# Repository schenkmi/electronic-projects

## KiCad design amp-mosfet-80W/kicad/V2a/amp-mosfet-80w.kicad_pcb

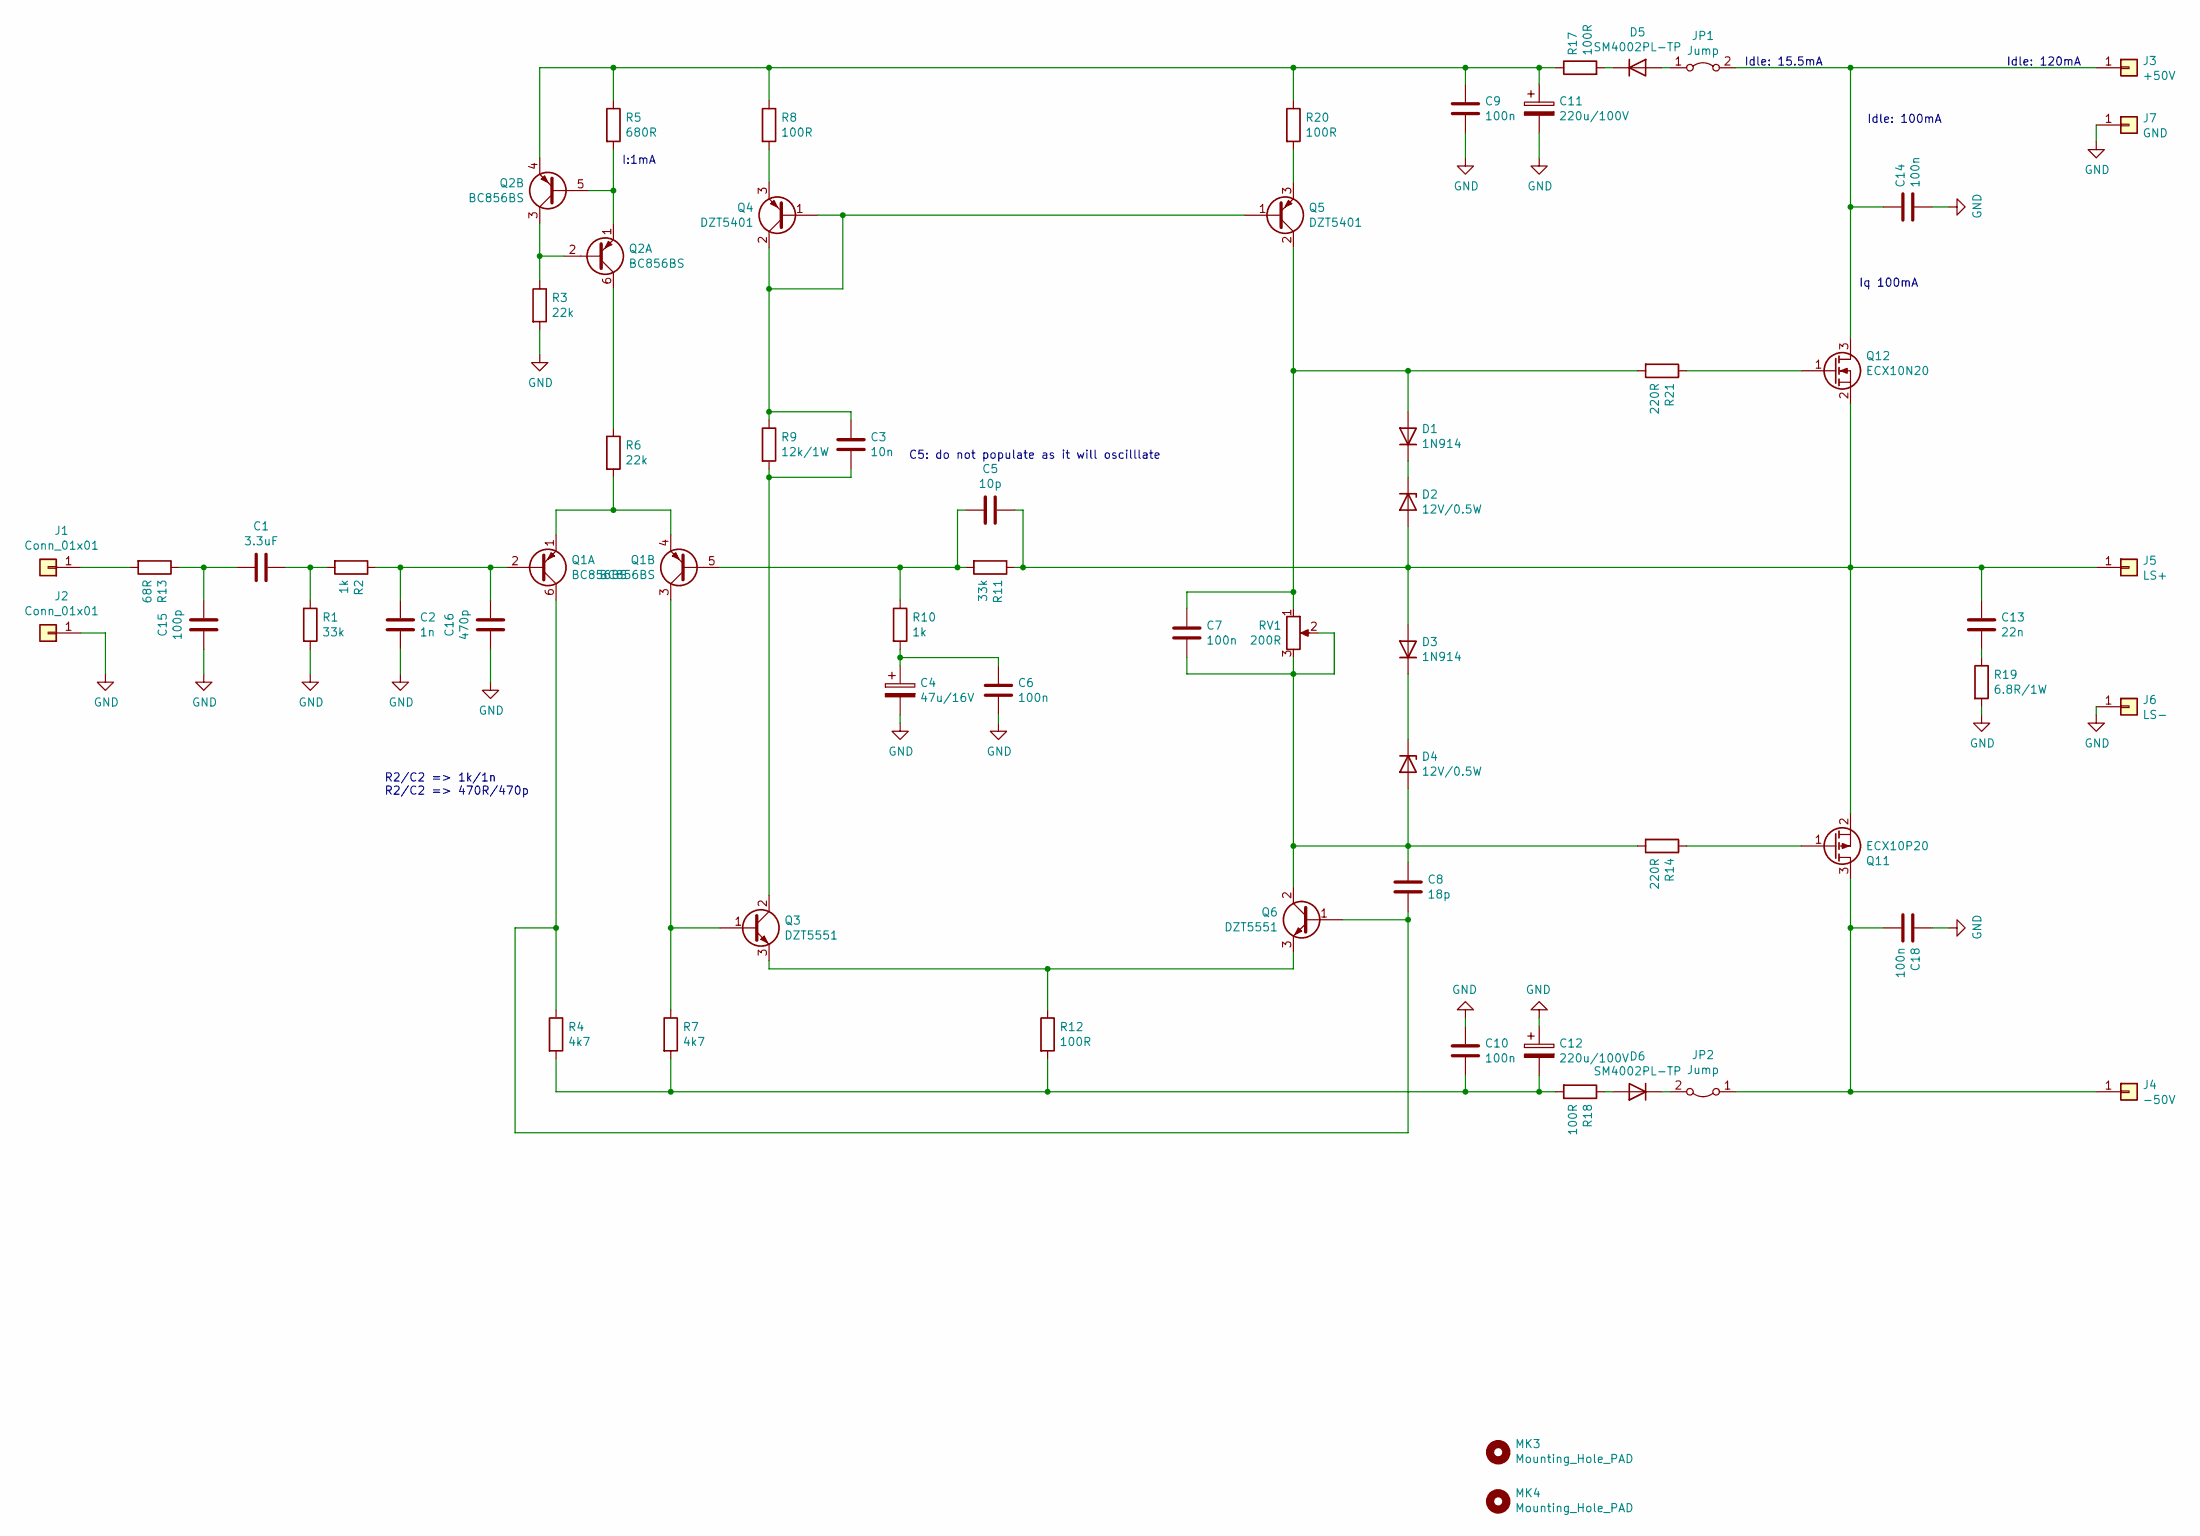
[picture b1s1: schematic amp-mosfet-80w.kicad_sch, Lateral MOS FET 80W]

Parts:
C1: 3.3uF; C_Rect_L7.2mm_W7.2mm_P5.00mm_FKS2_FKP2_MKS2_MKP2
C2: 1n; C_Rect_L7.2mm_W2.5mm_P5.00mm_FKS2_FKP2_MKS2_MKP2
C3: 10n; C_Rect_L7.2mm_W2.5mm_P5.00mm_FKS2_FKP2_MKS2_MKP2
C4: 47u/16V; CP_Radial_D5.0mm_P2.00mm
C5: 10p; C_0805_2012Metric_Pad1.18x1.45mm_HandSolder
C6, C7, C9, C10, C14, C18: 100n; C_Rect_L7.2mm_W2.5mm_P5.00mm_FKS2_FKP2_MKS2_MKP2
C8: 18p; C_0805_2012Metric_Pad1.18x1.45mm_HandSolder
C11, C12: 220u/100V; CP_Radial_D12.5mm_P5.00mm
C13: 22n; C_Rect_L7.2mm_W2.5mm_P5.00mm_FKS2_FKP2_MKS2_MKP2
C15: 100p; C_0805_2012Metric_Pad1.18x1.45mm_HandSolder
C16: 470p; C_0805_2012Metric_Pad1.18x1.45mm_HandSolder
D1, D3: 1N914; D_SOD-123
D2, D4: 12V/0.5W; D_SOD-123
D5, D6: SM4002PL-TP; D_SOD-123F
J1, J2: Conn_01x01; Pin_D1.0mm_L10.0mm
J3: +50V; SolderWire-1.5sqmm_1x01_D1.7mm_OD3.9mm
J4: -50V; SolderWire-1.5sqmm_1x01_D1.7mm_OD3.9mm
J5: LS+; SolderWire-1.5sqmm_1x01_D1.7mm_OD3.9mm
J6: LS-; SolderWire-1.5sqmm_1x01_D1.7mm_OD3.9mm
J7: GND; SolderWire-1.5sqmm_1x01_D1.7mm_OD3.9mm
JP1, JP2: Jump; PinHeader_1x02_P2.54mm_Vertical
MK3, MK4: Mounting_Hole_PAD; MountingHole_3.2mm_M3_Pad_Via
Q1, Q2: BC856BS; SOT-363_SC-70-6
Q3, Q6: DZT5551; SOT-223-3_TabPin2
Q4, Q5: DZT5401; SOT-223-3_TabPin2
Q11: ECX10P20; TO-247-3_Horizontal_TabUp
Q12: ECX10N20; TO-247-3_Horizontal_TabUp
R1, R11: 33k; R_0805_2012Metric_Pad1.20x1.40mm_HandSolder
R2, R10: 1k; R_0805_2012Metric_Pad1.20x1.40mm_HandSolder
R3, R6: 22k; R_0805_2012Metric_Pad1.20x1.40mm_HandSolder
R4, R7: 4k7; R_0805_2012Metric_Pad1.20x1.40mm_HandSolder
R5: 680R; R_0805_2012Metric_Pad1.20x1.40mm_HandSolder
R8, R12, R17, R18, R20: 100R; R_0805_2012Metric_Pad1.20x1.40mm_HandSolder
R9: 12k/1W; R_1206_3216Metric_Pad1.30x1.75mm_HandSolder
R13: 68R; R_0805_2012Metric_Pad1.20x1.40mm_HandSolder
R14, R21: 220R; R_0805_2012Metric_Pad1.20x1.40mm_HandSolder
R19: 6.8R/1W; R_MELF_MMB-0207
RV1: 200R; Potentiometer_Bourns_3296W_Vertical

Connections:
GND: C2.2, C4.2, C6.2, C9.2, C10.1, C11.2, C12.1, C14.2, C15.2, C16.2, C18.1, J2.1, J6.1, J7.1, R1.2, R3.2, R19.2
unnamed: C1.1, R1.1, R2.2
unnamed: C1.2, C15.1, R13.1
unnamed: C3.1, Q4.1 (B), Q4.2 (C), Q5.1 (B), R9.1
unnamed: C3.2, Q3.2 (C), R9.2
unnamed: C4.1, C6.1, R10.2
unnamed: C5.2, Q1.5 (B2), R10.1, R11.2
unnamed: C7.1, C8.2, D4.2 (A), Q6.2 (C), R14.2, RV1.2, RV1.3
unnamed: C7.2, D1.2 (A), Q5.2 (C), R21.2, RV1.1
unnamed: C8.1, Q1.6 (C1), Q6.1 (B), R4.1
unnamed: C10.2, C12.2, R4.2, R7.2, R12.2, R18.2
unnamed: C9.1, C11.1, Q2.4 (E2), R5.1, R8.1, R17.1, R20.1
unnamed: C5.1, C13.1, D2.2 (A), D3.2 (A), J5.1, Q11.2 (D), Q12.2 (S), R11.1
unnamed: C13.2, R19.1
unnamed: C14.1, J3.1, JP1.2 (B), Q12.3 (D)
unnamed: C2.1, C16.1, Q1.2 (B1), R2.1
unnamed: C18.2, J4.1, JP2.1 (A), Q11.3 (S)
unnamed: D1.1 (K), D2.1 (K)
unnamed: D3.1 (K), D4.1 (K)
unnamed: D5.1 (K), R17.2
unnamed: D5.2 (A), JP1.1 (A)
unnamed: D6.1 (K), JP2.2 (B)
unnamed: D6.2 (A), R18.1
unnamed: J1.1, R13.2
unnamed: Q1.1 (E1), Q1.4 (E2), R6.2
unnamed: Q1.3 (C2), Q3.1 (B), R7.1
unnamed: Q2.1 (E1), Q2.5 (B2), R5.2
unnamed: Q2.2 (B1), Q2.3 (C2), R3.1
unnamed: Q2.6 (C1), R6.1
unnamed: Q3.3 (E), Q6.3 (E), R12.1
unnamed: Q4.3 (E), R8.2
unnamed: Q5.3 (E), R20.2
unnamed: Q11.1 (G), R14.1
unnamed: Q12.1 (G), R21.1

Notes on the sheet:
C5: do not populate as it will oscilllate
Idle: 100mA
Iq 100mA
Idle: 15.5mA
Idle: 120mA
I:1mA
R2/C2 => 1k/1n R2/C2 => 470R/470p

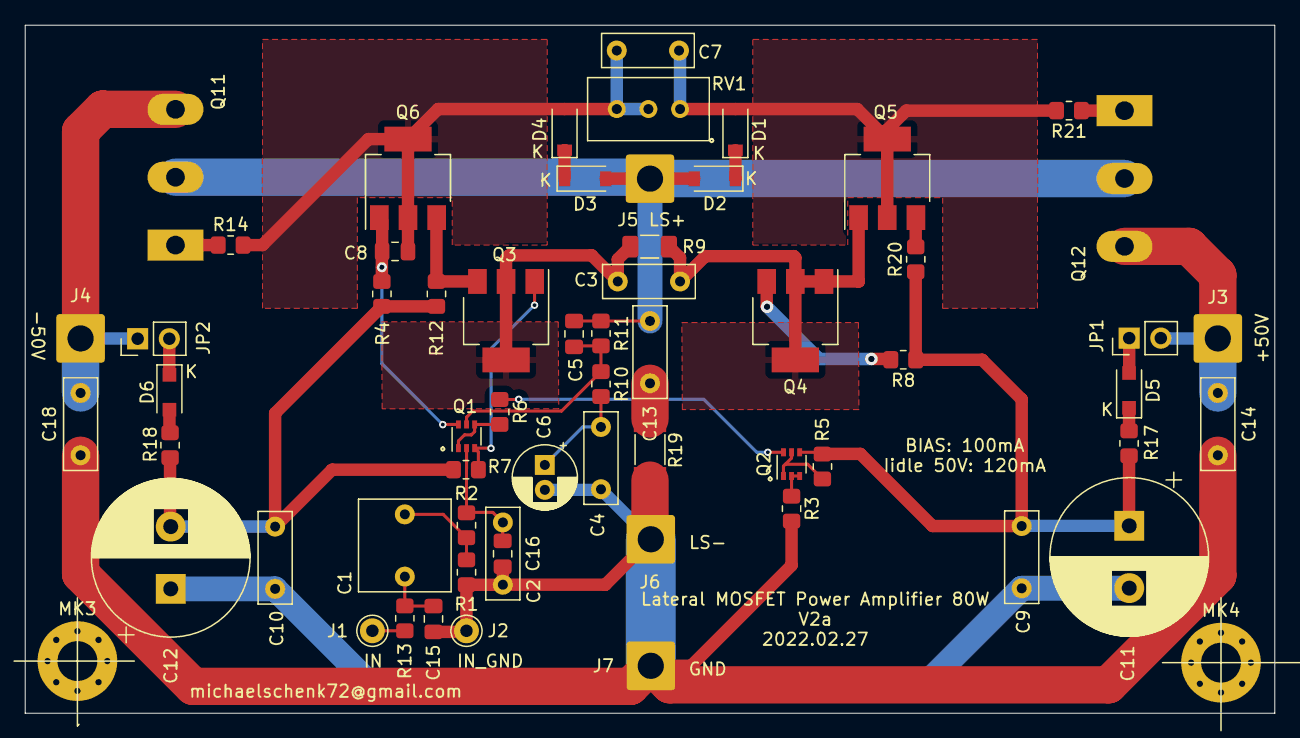
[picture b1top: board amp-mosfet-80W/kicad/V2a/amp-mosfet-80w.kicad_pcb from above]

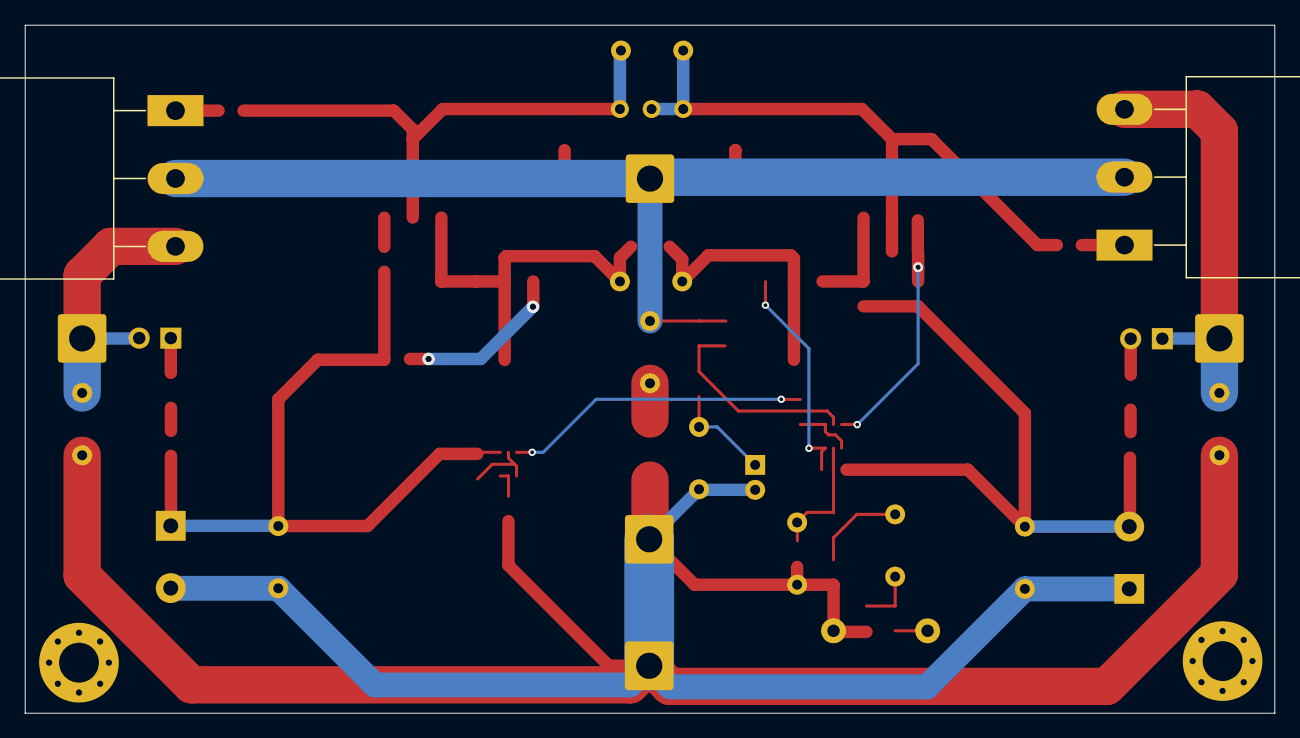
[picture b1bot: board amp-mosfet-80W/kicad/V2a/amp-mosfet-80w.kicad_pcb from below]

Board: 2 copper layers, 100.3 x 55.2 mm, 62 parts (2 on the bottom side), 34 nets.

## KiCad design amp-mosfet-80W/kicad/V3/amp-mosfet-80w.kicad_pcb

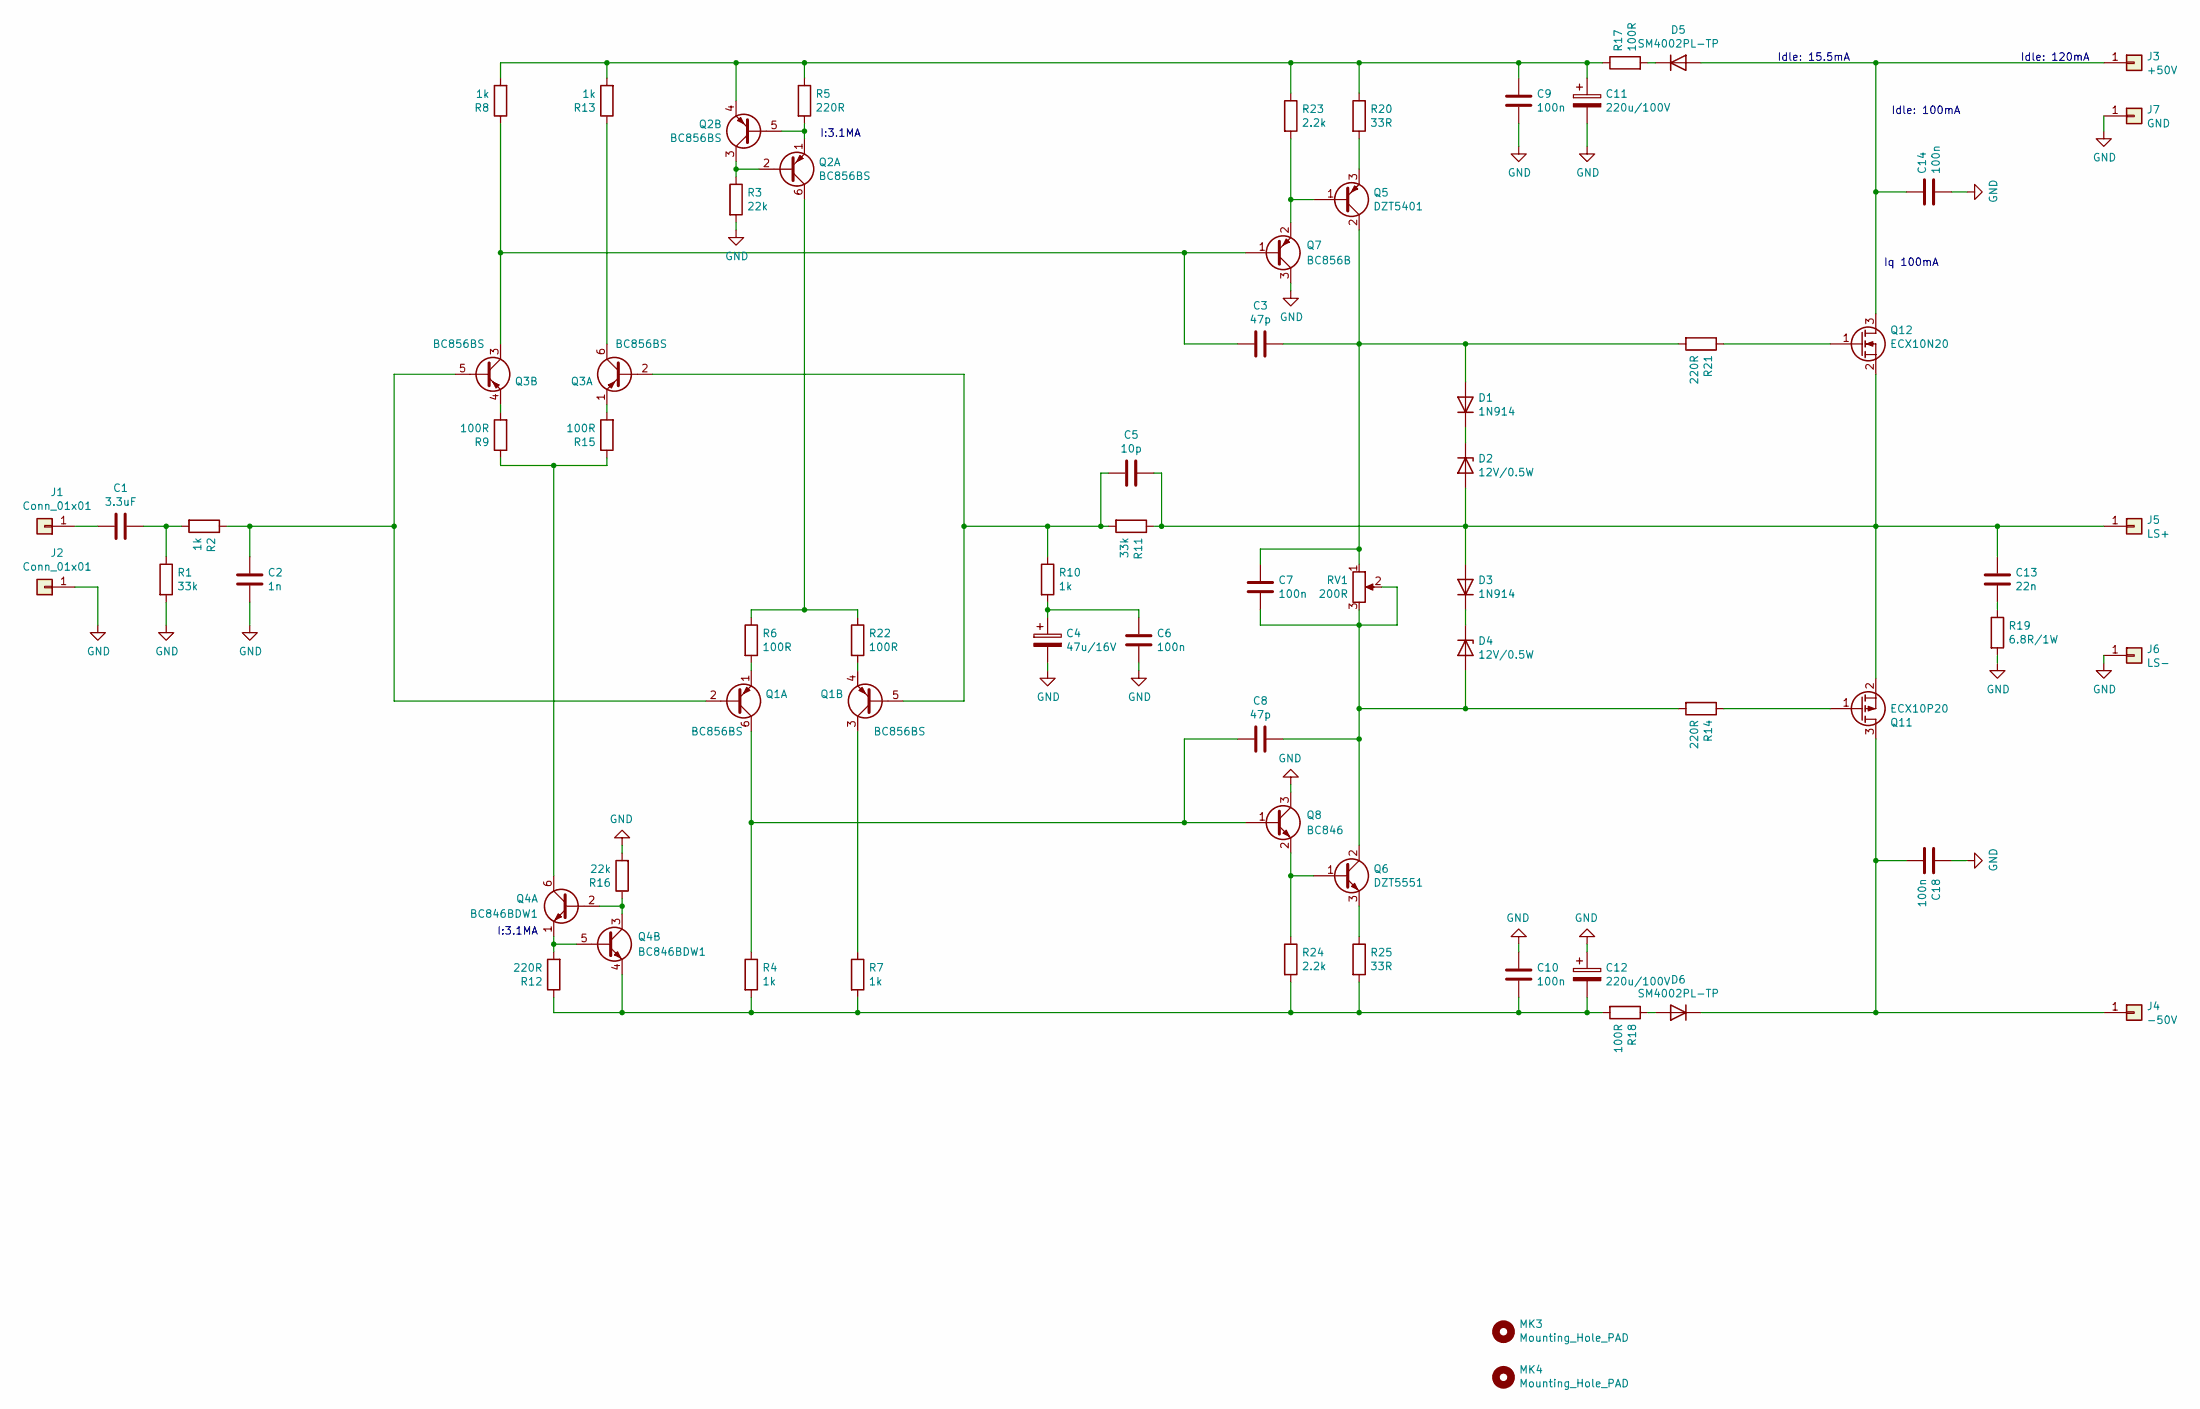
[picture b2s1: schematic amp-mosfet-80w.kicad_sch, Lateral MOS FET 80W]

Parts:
C1: 3.3uF; C_Rect_L7.2mm_W7.2mm_P5.00mm_FKS2_FKP2_MKS2_MKP2
C2: 1n; C_Rect_L7.2mm_W2.5mm_P5.00mm_FKS2_FKP2_MKS2_MKP2
C3, C8: 47p; C_0805_2012Metric_Pad1.18x1.45mm_HandSolder
C4: 47u/16V; CP_Radial_D5.0mm_P2.00mm
C5: 10p; C_0805_2012Metric_Pad1.18x1.45mm_HandSolder
C6, C7, C9, C10, C14, C18: 100n; C_Rect_L7.2mm_W2.5mm_P5.00mm_FKS2_FKP2_MKS2_MKP2
C11, C12: 220u/100V; CP_Radial_D12.5mm_P5.00mm
C13: 22n; C_Rect_L7.2mm_W2.5mm_P5.00mm_FKS2_FKP2_MKS2_MKP2
D1, D3: 1N914; D_SOD-123
D2, D4: 12V/0.5W; D_SOD-123
D5, D6: SM4002PL-TP; D_SOD-123F
J1, J2: Conn_01x01; Pin_D1.0mm_L10.0mm
J3: +50V; SolderWire-1.5sqmm_1x01_D1.7mm_OD3.9mm
J4: -50V; SolderWire-1.5sqmm_1x01_D1.7mm_OD3.9mm
J5: LS+; SolderWire-1.5sqmm_1x01_D1.7mm_OD3.9mm
J6: LS-; SolderWire-1.5sqmm_1x01_D1.7mm_OD3.9mm
J7: GND; SolderWire-1.5sqmm_1x01_D1.7mm_OD3.9mm
MK3, MK4: Mounting_Hole_PAD; MountingHole_3.2mm_M3_Pad_Via
Q1, Q2, Q3: BC856BS; SOT-363_SC-70-6
Q4: BC846BDW1; SOT-363_SC-70-6
Q5: DZT5401; SOT-223-3_TabPin2
Q6: DZT5551; SOT-223-3_TabPin2
Q7: BC856B; SOT-23
Q8: BC846; SOT-23
Q11: ECX10P20; TO-247-3_Horizontal_TabUp
Q12: ECX10N20; TO-247-3_Horizontal_TabUp
R1, R11: 33k; R_0805_2012Metric_Pad1.20x1.40mm_HandSolder
R2, R4, R7, R8, R10, R13: 1k; R_0805_2012Metric_Pad1.20x1.40mm_HandSolder
R3, R16: 22k; R_0805_2012Metric_Pad1.20x1.40mm_HandSolder
R5, R12, R14, R21: 220R; R_0805_2012Metric_Pad1.20x1.40mm_HandSolder
R6, R9, R15, R17, R18, R22: 100R; R_0805_2012Metric_Pad1.20x1.40mm_HandSolder
R19: 6.8R/1W; R_MELF_MMB-0207
R20, R25: 33R; R_0805_2012Metric_Pad1.20x1.40mm_HandSolder
R23, R24: 2.2k; R_0805_2012Metric_Pad1.20x1.40mm_HandSolder
RV1: 200R; Potentiometer_Bourns_3296W_Vertical

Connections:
GND: C2.2, C4.2, C6.2, C9.2, C10.1, C11.2, C12.1, C14.2, C18.1, J2.1, J6.1, J7.1, Q7.3 (C), Q8.3 (C), R1.2, R3.2, R16.2, R19.2
unnamed: C1.1, R1.1, R2.2
unnamed: C1.2, J1.1
unnamed: C3.2, Q3.3 (C2), Q7.1 (B), R8.1
unnamed: C4.1, C6.1, R10.2
unnamed: C7.1, C8.1, D4.2 (A), Q6.2 (C), R14.2, RV1.2, RV1.3
unnamed: C3.1, C7.2, D1.2 (A), Q5.2 (C), R21.2, RV1.1
unnamed: C10.2, C12.2, Q4.4 (E2), R4.2, R7.2, R12.1, R18.2, R24.2, R25.2
unnamed: C9.1, C11.1, Q2.4 (E2), R5.1, R8.2, R13.2, R17.1, R20.1, R23.1
unnamed: C5.1, C13.1, D2.2 (A), D3.2 (A), J5.1, Q11.2 (D), Q12.2 (S), R11.1
unnamed: C13.2, R19.1
unnamed: C14.1, D5.2 (A), J3.1, Q12.3 (D)
unnamed: D1.1 (K), D2.1 (K)
unnamed: D3.1 (K), D4.1 (K)
unnamed: D5.1 (K), R17.2
unnamed: C18.2, D6.1 (K), J4.1, Q11.3 (S)
unnamed: D6.2 (A), R18.1
unnamed: Q1.1 (E1), R6.2
unnamed: C2.1, Q1.2 (B1), Q3.5 (B2), R2.1
unnamed: Q1.4 (E2), R22.2
unnamed: C5.2, Q1.5 (B2), Q3.2 (B1), R10.1, R11.2
unnamed: C8.2, Q1.6 (C1), Q8.1 (B), R4.1
unnamed: Q2.1 (E1), Q2.5 (B2), R5.2
unnamed: Q2.2 (B1), Q2.3 (C2), R3.1
unnamed: Q3.1 (E1), R15.2
unnamed: Q3.4 (E2), R9.2
unnamed: Q3.6 (C1), R13.1
unnamed: Q4.1 (E1), Q4.5 (B2), R12.2
unnamed: Q4.2 (B1), Q4.3 (C2), R16.1
unnamed: Q4.6 (C1), R9.1, R15.1
unnamed: Q5.1 (B), Q7.2 (E), R23.2
unnamed: Q5.3 (E), R20.2
unnamed: Q6.1 (B), Q8.2 (E), R24.1
unnamed: Q6.3 (E), R25.1
unnamed: Q11.1 (G), R14.1
unnamed: Q12.1 (G), R21.1
unnamed: Q2.6 (C1), R6.1, R22.1
unnamed: Q1.3 (C2), R7.1

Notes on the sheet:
I:3.1MA
Idle: 100mA
Iq 100mA
Idle: 15.5mA
Idle: 120mA

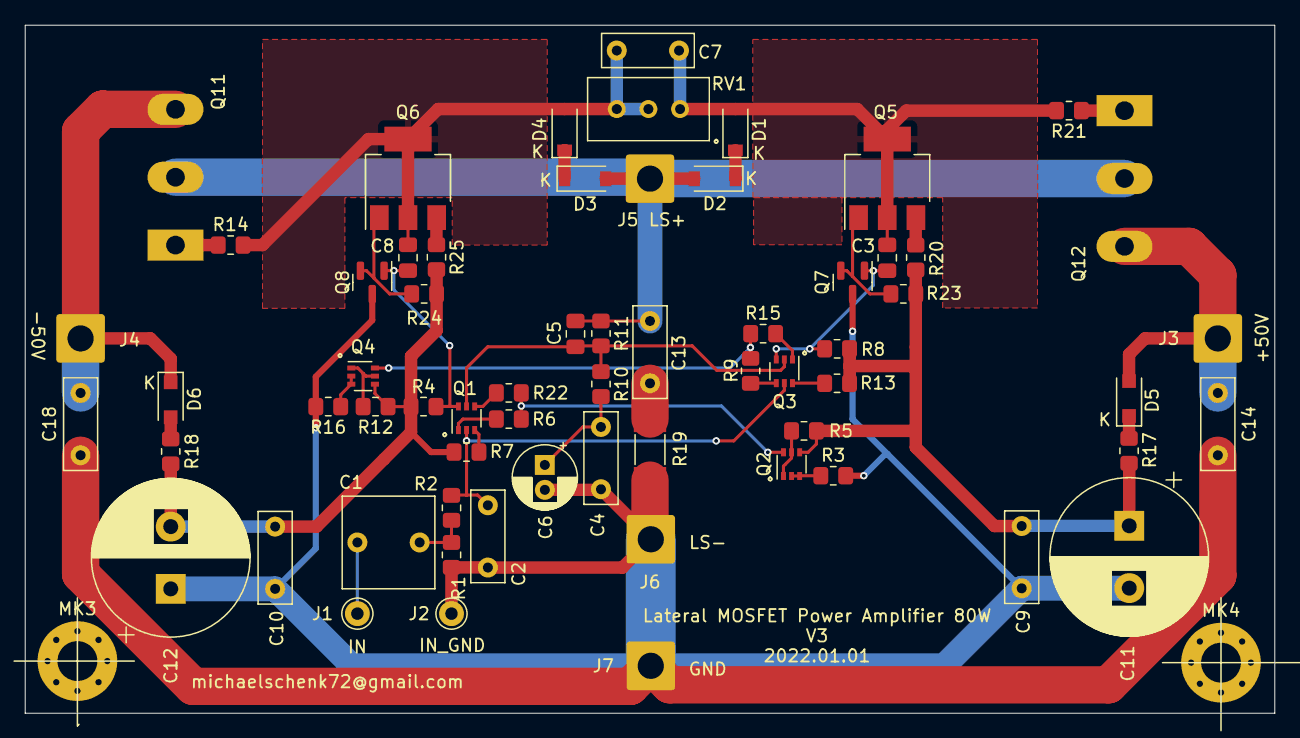
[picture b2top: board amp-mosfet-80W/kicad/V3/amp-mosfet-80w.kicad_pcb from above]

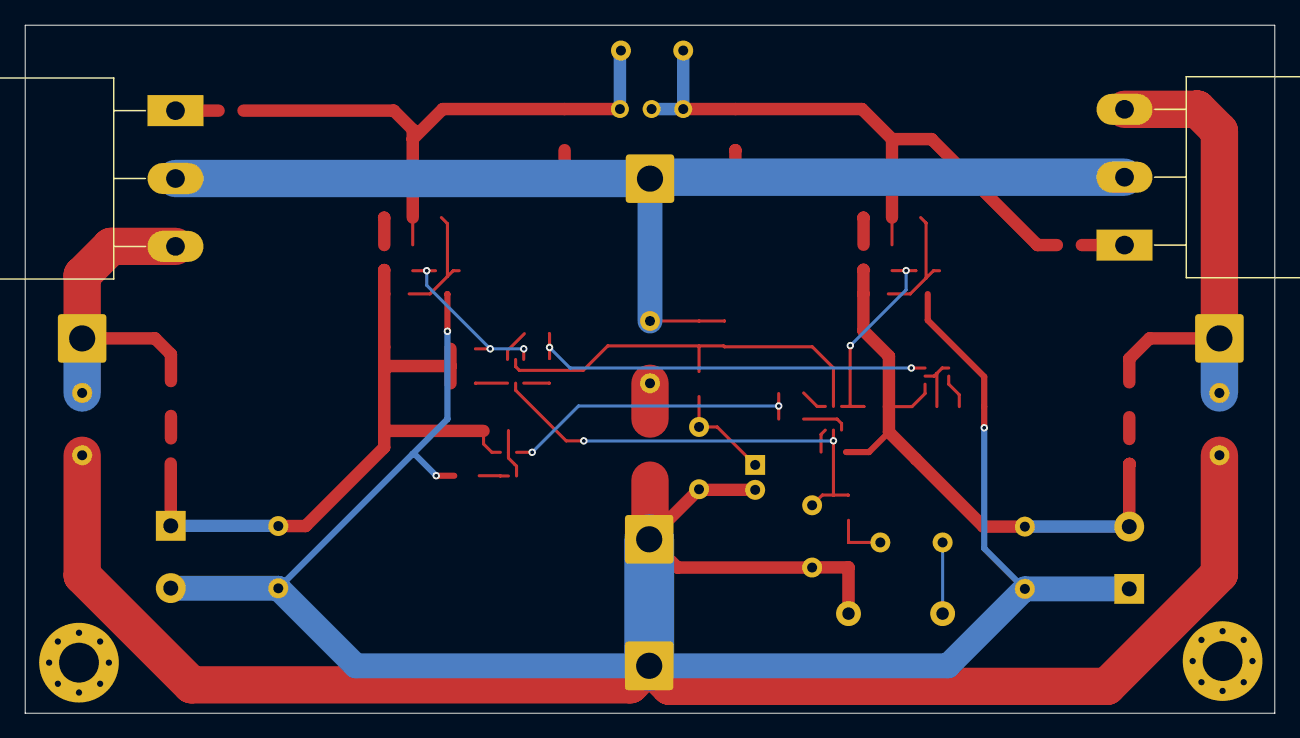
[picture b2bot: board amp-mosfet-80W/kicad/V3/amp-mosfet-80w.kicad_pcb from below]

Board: 2 copper layers, 100.3 x 55.2 mm, 66 parts (2 on the bottom side), 38 nets.
